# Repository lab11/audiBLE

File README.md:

# audiBLE
Bluetooth Low Energy audio sensing shield for squall

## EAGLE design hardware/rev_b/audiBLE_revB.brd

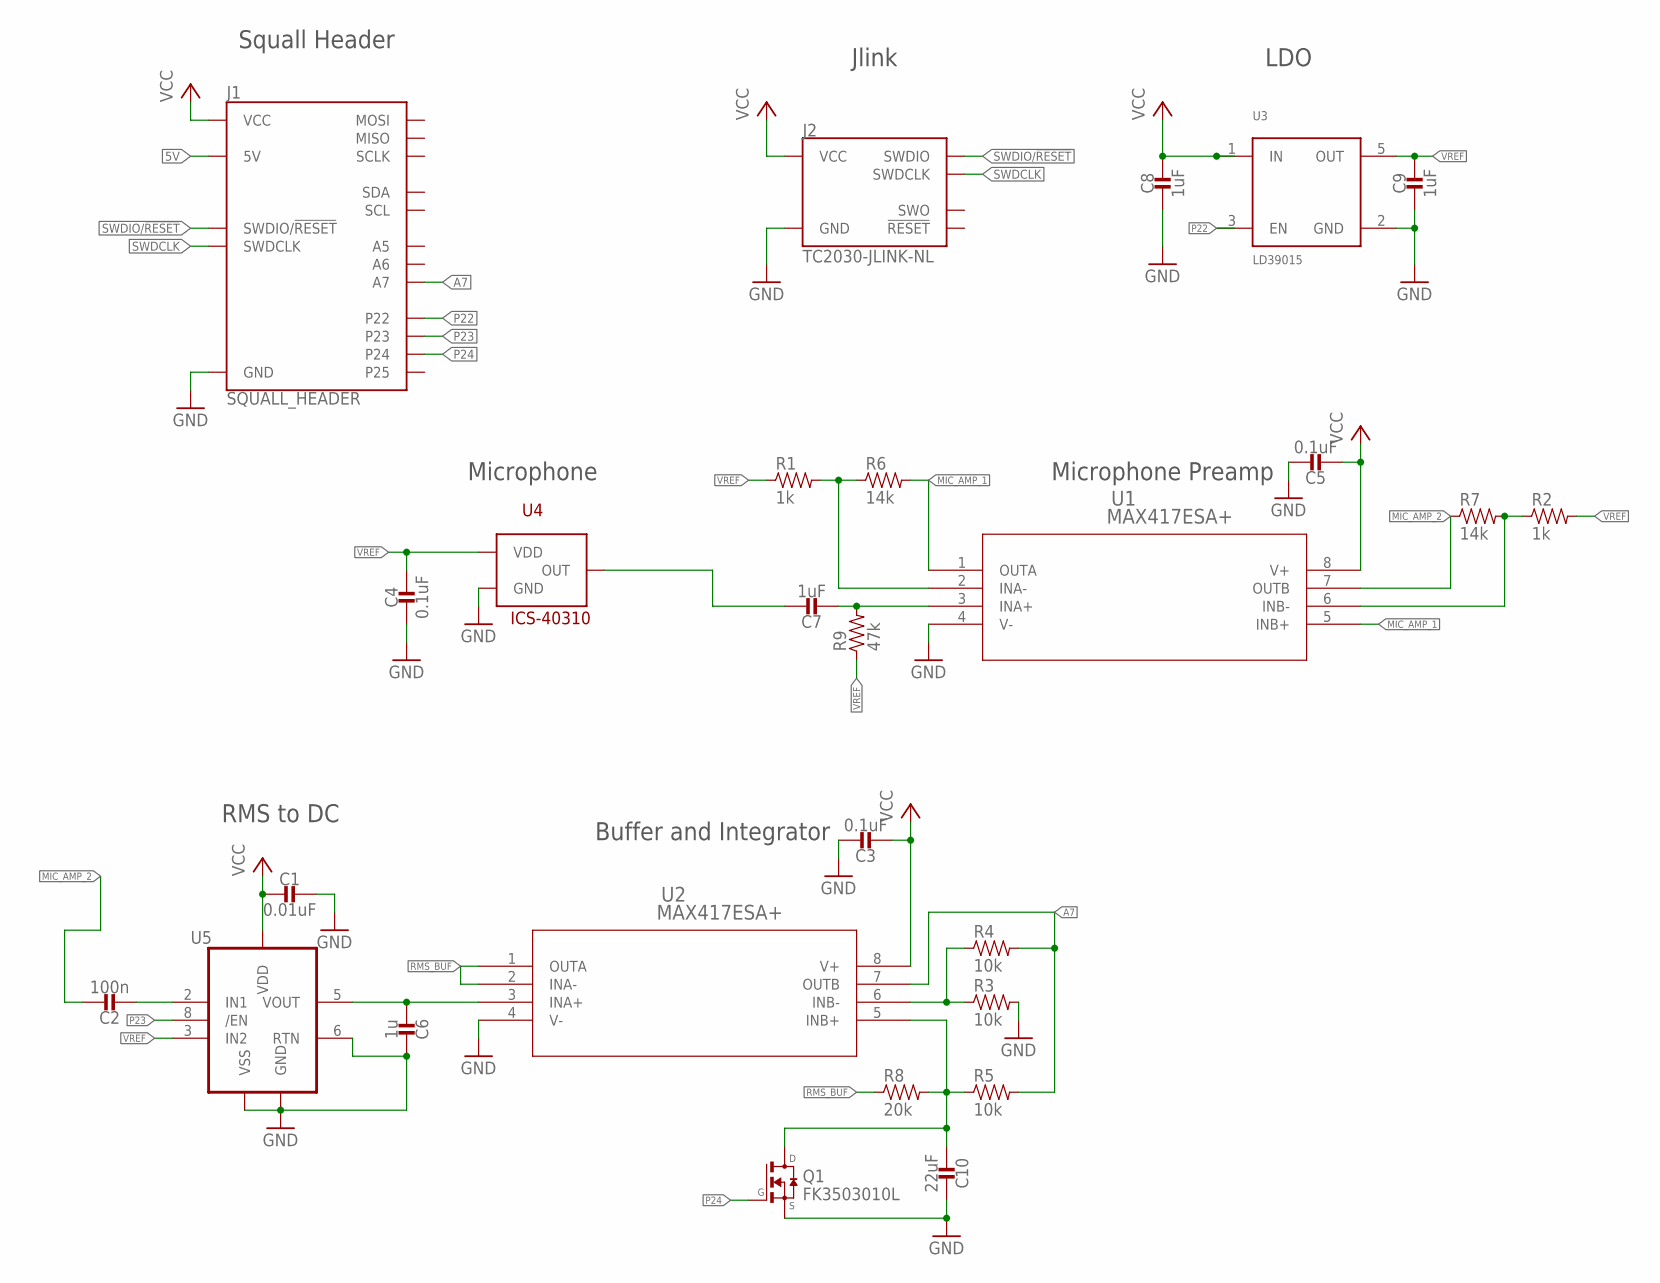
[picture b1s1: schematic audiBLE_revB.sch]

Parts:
C1: 0.01uF; 0402_CAP
C2: 100n; 0402_CAP
C3, C4, C5: 0.1uF; 0402_CAP
C6: 1u; 0402_CAP
C7, C8, C9: 1uF; 0402_CAP
C10: 22uF; 0402_CAP
J1: SQUALL_HEADER
J2: TC2030-JLINK-NL; TC2030-IDC-NL
Q1: FK3503010L; SC85
R1, R2: 1k; 0402_RES
R3, R4, R5: 10k; 0402_RES
R6, R7: 14k; 0402_RES
R8: 20k; 0402_RES
R9: 47k; 0402_RES
U1, U2: MAX417ESA+; 21-0041B_8
U3: LD39015; SOT-23-5
U4: ICS-40310; LGA_CAV3
U5: LTC1966CMS8; MSOP8

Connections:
5V: J1.A5 (5V), J1.A7 (5V)
A7: J1.B5 (A7), R4.2, R5.2, U2.7 (OUTB)
GND: C1.1, C3.1, C4.2, C5.1, C6.1, C8.2, C9.2, C10.1, J1.A9 (GND), J1.A10 (GND), J2.5 (GND), Q1.2 (S), R3.2, U1.4 (V-), U2.4 (V-), U3.2 (GND), U4.P$2 (GND), U5.1 (GND), U5.4 (VSS), U5.6 (RTN)
MIC: C7.1, U4.P$1 (OUT)
MIC_AMP_1: R6.2, U1.1 (OUTA), U1.5 (INB+)
MIC_AMP_2: C2.1, R7.1, U1.7 (OUTB)
unnamed: C7.2, R9.2, U1.3 (INA+)
unnamed: C2.2, U5.2 (IN1)
unnamed: C6.2, U2.3 (INA+), U5.5 (VOUT)
unnamed: R1.2, R6.1, U1.2 (INA-)
unnamed: R2.1, R7.2, U1.6 (INB-)
unnamed: R3.1, R4.1, U2.6 (INB-)
unnamed: C10.2, Q1.3 (D), R5.1, R8.2, U2.5 (INB+)
P22: J1.A2 (P22), U3.3 (EN)
P23: J1.A4 (P23), U5.8 (/EN)
P24: J1.A6 (P24), Q1.1 (G)
RMS_BUF: R8.1, U2.1 (OUTA), U2.2 (INA-)
SWDCLK: J1.B2 (SWDCLK), J2.4 (SWDCLK)
SWDIO/!RESET: J1.B4 (SWDIO/!RESET), J2.2 (SWDIO)
VCC: C1.2, C3.2, C5.2, C8.1, J1.A1 (VCC), J1.A3 (VCC), J2.1 (VCC), U1.8 (V+), U2.8 (V+), U3.1 (IN), U5.7 (VDD)
VREF: C4.1, C9.1, R1.1, R2.2, R9.1, U3.5 (OUT), U4.P$3 (VDD), U5.3 (IN2)

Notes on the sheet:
Squall Header
Microphone
Microphone Preamp
Jlink
LDO
RMS to DC
Buffer and Integrator

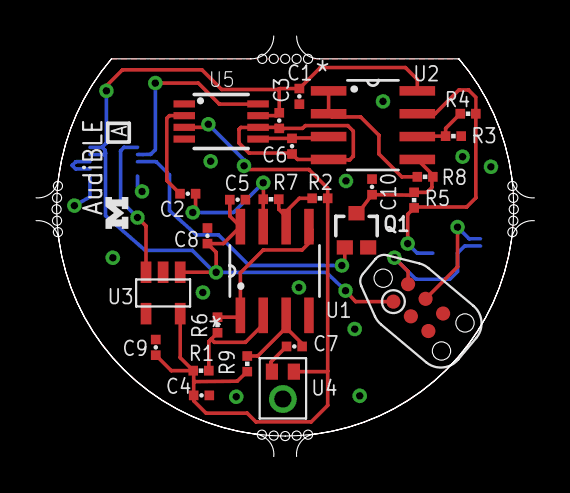
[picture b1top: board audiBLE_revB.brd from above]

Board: 2 copper layers, 27.7 x 23.4 mm, 28 parts (0 on the bottom side), 21 nets.

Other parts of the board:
U$1: UMICH_SOLID_50MIL

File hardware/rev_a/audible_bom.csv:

# Bill of Materials
# Converted from audible_bom.xlsx
# Generated by bom_to_text.py

,Qty,Value,Device,Package,Parts,Description,DIGIKEY,MOUSER,NEWARK
a,2,SQUALL_HEADER,SQUALL_HEADER,SQUALL_HEADER,J1,Header for a sensor board on top of the Squall BLE tag board.,H11617CT-ND,,
a,2,1k,RESISTOR0402_RES,0402_RES,"R1, R2",0402 Resistor,RHM1.0KCECT-ND,,
a,3,10k,RESISTOR0402_RES,0402_RES,"R3, R4, R5",0402 Resistor,RHM10.0KCDCT-ND,,
a,2,14k,RESISTOR0402_RES,0402_RES,"R6, R7",0402 Resistor,RHM14KCDCT-ND,,
a,1,20k,RESISTOR0402_RES,0402_RES,R8,0402 Resistor,RHM20.0KCDCT-ND,,
a,1,47k,RESISTOR0402_RES,0402_RES,R9,0402 Resistor,RHM47KCECT-ND,,
a,2,10nF,CAPACITOR,0402_CAP,C1,0402 Capacitor,490-6318-1-ND,,
a,4,100nF,CAPACITOR,0402_CAP,"C2, C3, C4, C5",0402 Capacitor,1276-1442-1-ND,,
a,4,1uF,CAPACITOR,0402_CAP,"C6, C7, C8, C9",0402 Capacitor,490-6281-1-ND,,
a,1,22uF,CAPACITOR,0402_CAP,C10,0402 Capacitor,1276-6804-1-ND,,
a,2,MAX417ESA+,MAX417ESA+,21-0041B_8,"U1, U2",Max417 Op Amp,MAX417ESA+-ND,,
a,1,LD39015,LD39015,SOT-23-5,U3,LD39015 1.2V LDO,497-6871-1-ND,,
a,1,ICS-40310,ICS-40310,LGA_CAV3,U4,Invensence ICS-40310 MEMS Mic,1428-1028-1-ND,,
a,1,LTC1966CMS8,LTC1966CMS8,MSOP8,U5,Linear Technology RMS-to-DC convert,LTC1966CMS8#PBF-ND,,
a,1,FK3503010L,FK3503010L,SC85,Q1,NMOS Transistor,FK3503010LCT-ND,,
,,,,,,,,,
,,(a)udible,,,,,,,
,,(s)quall,,,,,,,
,,(l)ed box,,,,,,,
,,(o)bserver,,,,,,,
,,(x) did not populate,,,,,,,

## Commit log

2016-08-03 Added Simulation file
2016-08-04 added mic sample
2016-08-05 Updated sim for new version of ltspice
2016-08-08 working sim
2016-08-08 Starting eagle schematic
2016-08-08 sim altered from waveforms
2016-08-09 ripped up blees board
2016-08-09 Upped Vref to 1.2V
2016-08-09 Almost completed schematic
2016-08-09 better layout
2016-08-09 better schematic
2016-08-09 Updated sch and brd
2016-08-10 almost routed
2016-08-10 routed
2016-08-10 fixed clearance issues from wrong wire width
2016-08-10 Removed headers and fixed wire angles
2016-08-10 Cleaned up routes all over
2016-08-10 Fixed ref names
2016-08-10 Finished
2016-08-11 Added BOM and copied over panel files from blees
2016-08-11 updted BOM
2016-08-11 Updated Part Names and digikey part names
2016-08-11 added files for eagle.py
2016-08-11 add audible zips
2016-08-11 removed gerbers
2016-08-11 aded BOM files
2016-08-11 added panel gerbers
2016-08-15 Cleaning repo
2016-08-15 Including wav files for simulation in repo
2016-08-15 inital commit derived from blees and blink
2016-08-15 Added nrf5x-base submodule
2016-08-15 added ADC
2016-08-16 Implemented platform functions and used them inside the audible app
2016-08-16 Initial summon commit based on blink
2016-08-16 Updated Makefile and readme
2016-08-16 Changing blink's summon for audiBLE
2016-08-16 Learned how buffers work in NodeJS
2016-08-17 parse object and populate index.html
2016-08-19 changes made to work with summon
2016-10-02 Updated readme
    Changed it to mention that it's a squall shield
2017-04-20 Added rev_b schematic and board files to reflect changes in connections on R4
2017-05-31 Added summary of work and stairwell data
    Added a formal summary of the work that I completed on AudiBLE
    Added two spreadsheets of the audio data I collected while experimenting in the BBB stairwell
